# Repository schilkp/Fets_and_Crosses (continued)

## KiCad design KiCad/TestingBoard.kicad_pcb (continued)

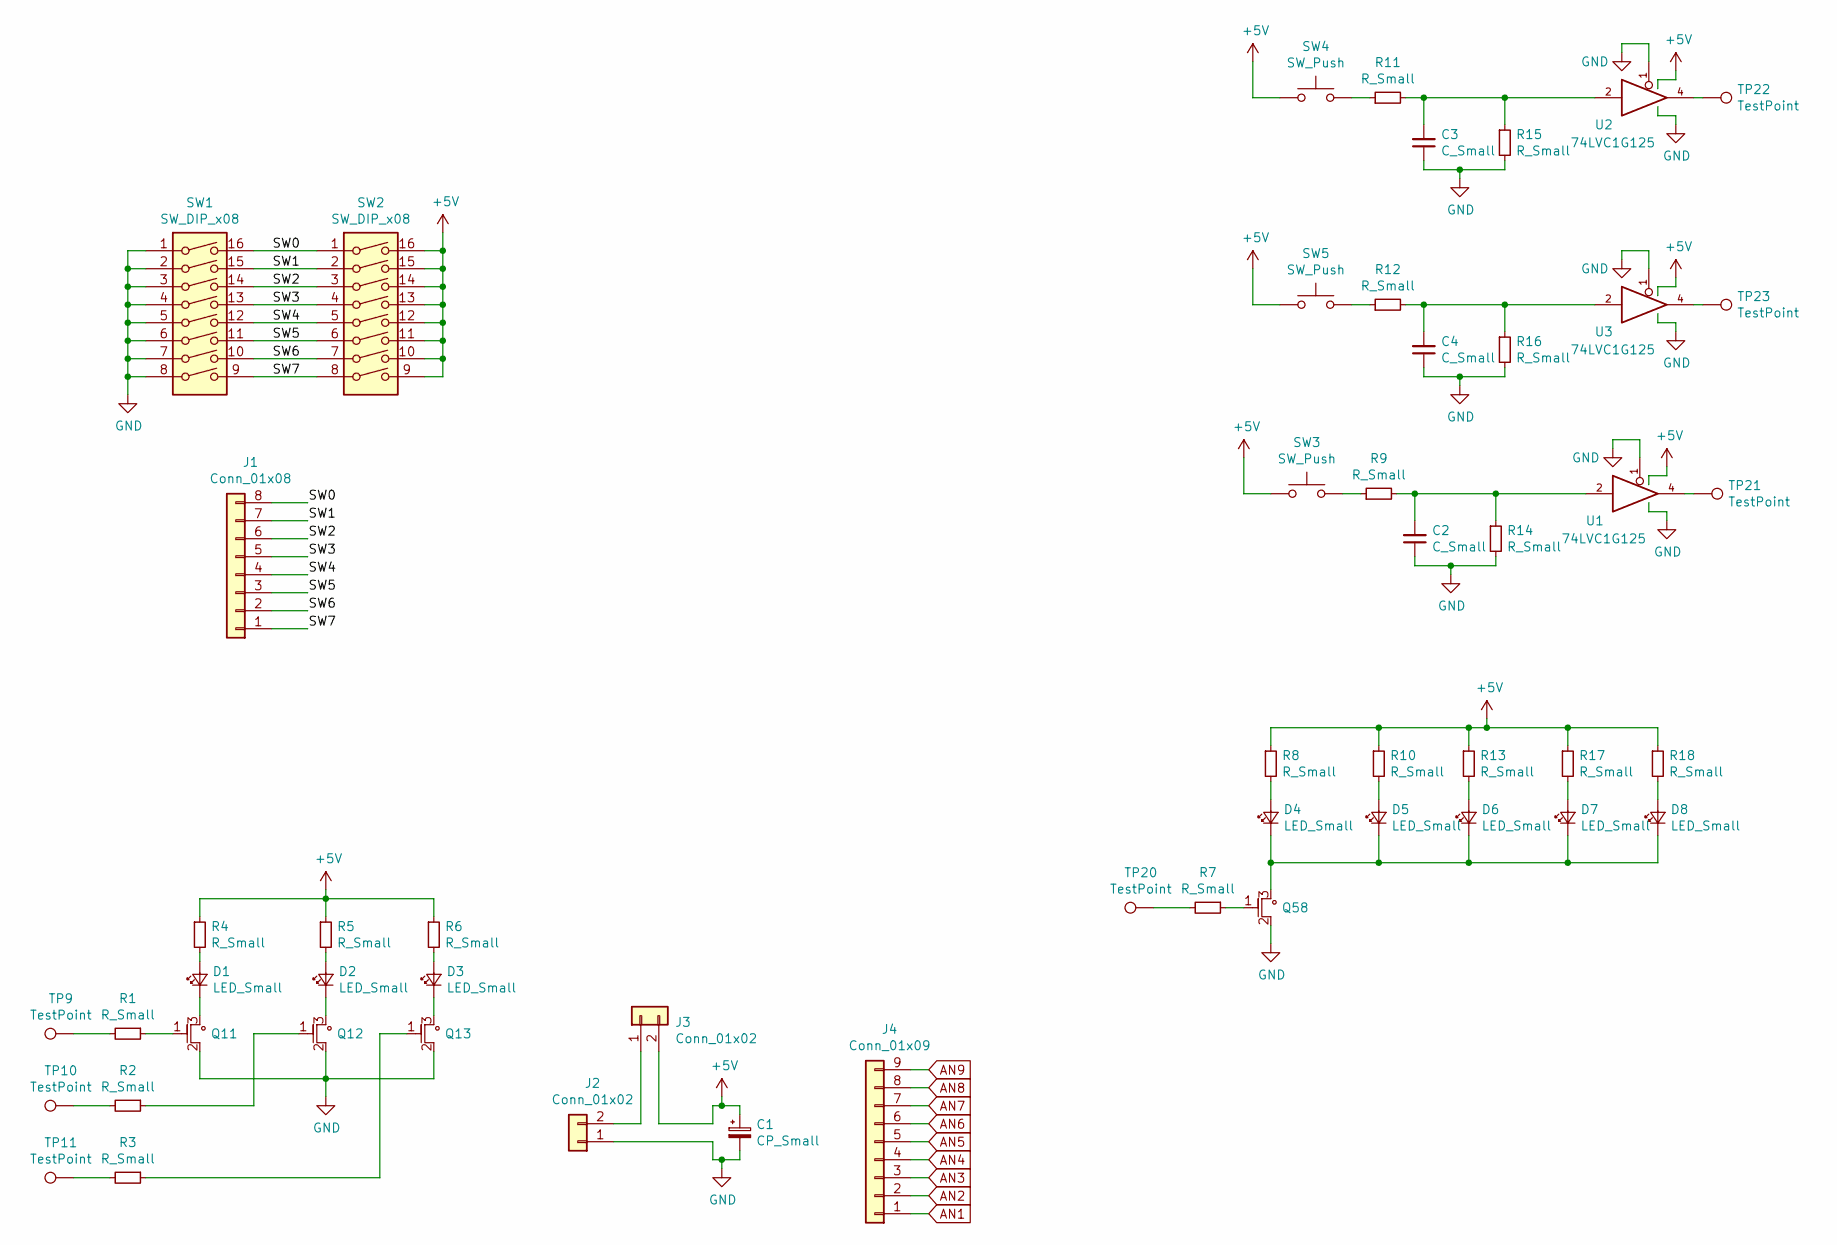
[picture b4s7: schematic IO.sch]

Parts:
C1: CP_Small; CP_Elec_8x6.5
C2, C3, C4: C_Small; C_0603_1608Metric
D1, D2, D3, D4, D5, D6, D7, D8: LED_Small; LED_0805_2012Metric
J1: Conn_01x08; PinHeader_1x08_P2.54mm_Vertical
J2, J3: Conn_01x02; PinHeader_1x02_P2.54mm_Vertical
J4: Conn_01x09; PinHeader_1x09_P2.54mm_Vertical
Q11, Q12, Q13, Q58: NM; SOT-23-N
R1, R2, R3, R4, R5, R6, R7, R8, R9, R10, R11, R12, R13, R14, R15, R16, R17, R18: R_Small; R_0603_1608Metric
SW1, SW2: SW_DIP_x08; DIP-16_W7.62mm
SW3, SW4, SW5: SW_Push; SW_PUSH_6mm
TP9, TP10, TP11, TP20, TP21, TP22, TP23: TestPoint; PinSocket_1x01_P2.54mm_Vertical
U1, U2, U3: 74LVC1G125; TSOP-5_1.65x3.05mm_P0.95mm

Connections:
+5V: C1.1, J3.2, R4.1, R5.1, R6.1, R8.1, R10.1, R13.1, R17.1, R18.1, SW2.9, SW2.10, SW2.11, SW2.12, SW2.13, SW2.14, SW2.15, SW2.16, SW3.1, SW4.1, SW5.1, U1.5 (VCC), U2.5 (VCC), U3.5 (VCC); also elsewhere on the board
/IO.sch/SW0: J1.8, SW1.16, SW2.1
/IO.sch/SW1: J1.7, SW1.15, SW2.2
/IO.sch/SW2: J1.6, SW1.14, SW2.3
/IO.sch/SW3: J1.5, SW1.13, SW2.4
/IO.sch/SW4: J1.4, SW1.12, SW2.5
/IO.sch/SW5: J1.3, SW1.11, SW2.6
/IO.sch/SW6: J1.2, SW1.10, SW2.7
/IO.sch/SW7: J1.1, SW1.9, SW2.8
AN1: J4.1; also elsewhere on the board
AN2: J4.2; also elsewhere on the board
AN3: J4.3; also elsewhere on the board
AN4: J4.4; also elsewhere on the board
AN5: J4.5; also elsewhere on the board
AN6: J4.6; also elsewhere on the board
AN7: J4.7; also elsewhere on the board
AN8: J4.8; also elsewhere on the board
AN9: J4.9; also elsewhere on the board
GND: C1.2, C2.1, C3.1, C4.1, J2.1, Q11.2, Q12.2, Q13.2, Q58.2, R14.2, R15.2, R16.2, SW1.1, SW1.2, SW1.3, SW1.4, SW1.5, SW1.6, SW1.7, SW1.8, U1.1, U1.3 (GND), U2.1, U2.3 (GND), U3.1, U3.3 (GND); also elsewhere on the board
unnamed: C2.2, R9.2, R14.1, U1.2
unnamed: C3.2, R11.2, R15.1, U2.2
unnamed: C4.2, R12.2, R16.1, U3.2
unnamed: D1.1 (K), Q11.3
unnamed: D1.2 (A), R4.2
unnamed: D2.1 (K), Q12.3
unnamed: D2.2 (A), R5.2
unnamed: D3.1 (K), Q13.3
unnamed: D3.2 (A), R6.2
unnamed: D4.1 (K), D5.1 (K), D6.1 (K), D7.1 (K), D8.1 (K), Q58.3
unnamed: D4.2 (A), R8.2
unnamed: D5.2 (A), R10.2
unnamed: D6.2 (A), R13.2
unnamed: D7.2 (A), R17.2
unnamed: D8.2 (A), R18.2
unnamed: J2.2, J3.1
unnamed: Q11.1, R1.1
unnamed: Q12.1, R2.1
unnamed: Q13.1, R3.1
unnamed: Q58.1, R7.1
unnamed: R1.2, TP9.1
unnamed: R2.2, TP10.1
unnamed: R3.2, TP11.1
unnamed: R7.2, TP20.1
unnamed: R9.1, SW3.2
unnamed: R11.1, SW4.2
unnamed: R12.1, SW5.2
unnamed: TP21.1, U1.4
unnamed: TP22.1, U2.4
unnamed: TP23.1, U3.4

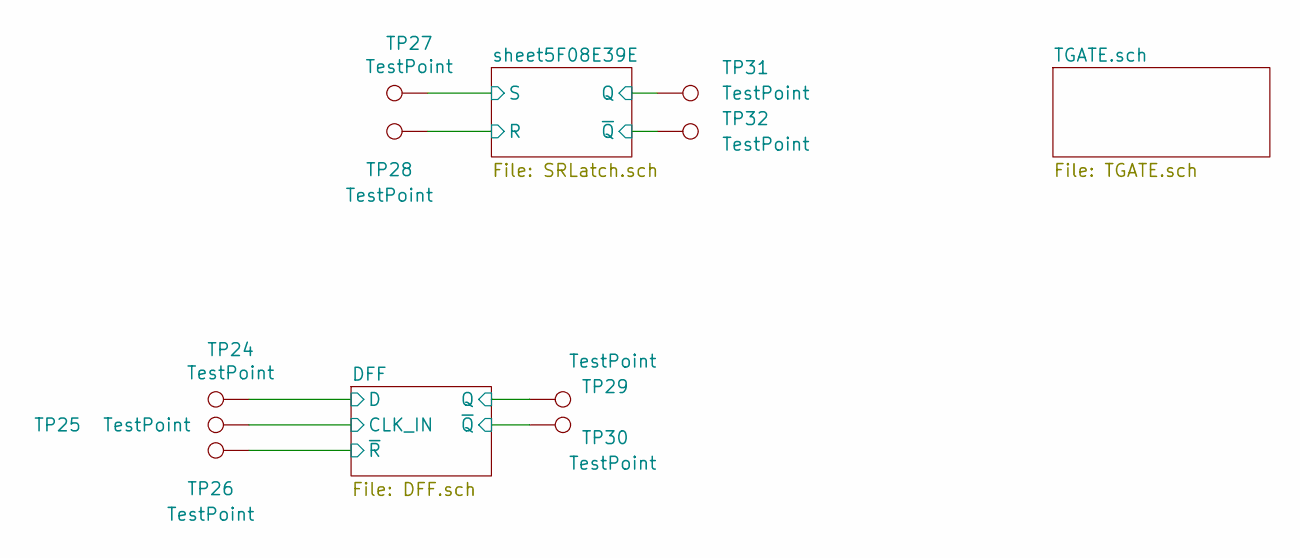
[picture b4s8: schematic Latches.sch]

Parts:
TP24, TP25, TP26, TP27, TP28, TP29, TP30, TP31, TP32: TestPoint; PinSocket_1x01_P2.54mm_Vertical

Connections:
/Sheet5F08E132/DFF/CLK_IN: TP25.1; also elsewhere on the board
/Sheet5F08E132/DFF/D: TP24.1; also elsewhere on the board
/Sheet5F08E132/DFF/Q: TP29.1; also elsewhere on the board
/Sheet5F08E132/DFF/~Q: TP30.1; also elsewhere on the board
/Sheet5F08E132/DFF/~R: TP26.1; also elsewhere on the board
/Sheet5F08E132/sheet5F08E39E/Q: TP31.1; also elsewhere on the board
/Sheet5F08E132/sheet5F08E39E/R: TP28.1; also elsewhere on the board
/Sheet5F08E132/sheet5F08E39E/S: TP27.1; also elsewhere on the board
/Sheet5F08E132/sheet5F08E39E/~Q: TP32.1; also elsewhere on the board

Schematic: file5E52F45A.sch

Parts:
Q97, Q99, Q100, Q101, Q102, Q103, Q104, Q105, Q106: PM; SOT-23-P
Q98, Q107, Q108, Q109, Q110, Q111, Q112, Q113, Q114: NM; SOT-23-N
R19, R20, R21, R22, R23, R24, R25, R26, R27, R28, R29, R30, R31, R32, R33, R34, R35, R36: R_Small; R_0603_1608Metric_NOLBL
TP38, TP39, TP40, TP41, TP42, TP43, TP44, TP45, TP46, TP47, TP48, TP49, TP50, TP51, TP52, TP53, TP54, TP55, TP56, TP57, TP58, TP59, TP60, TP61, TP62, TP63, TP64, TP65, TP66, TP67, TP68, TP69, TP70, TP71, TP72, TP73, TP74, TP75, TP76, TP77, TP78, TP79, TP80, TP81, TP82, TP83, TP84, TP85, TP86, TP87, TP88, TP89, TP90, TP91, TP92, TP93, TP94, TP95, TP96, TP97, TP98, TP99, TP100, TP101, TP102, TP103, TP104, TP105, TP106, TP107, TP108, TP109, TP110, TP111, TP112, TP113, TP114, TP115, TP116, TP117, TP118, TP119, TP120, TP121, TP122, TP123, TP124, TP125, TP126, TP127: TestPoint; TestPoint_Pad_1.5x1.5mm_NOLBL

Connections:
unnamed: Q97.1, TP38.1
unnamed: Q97.2, TP40.1
unnamed: Q97.3, TP39.1
unnamed: Q98.1, TP65.1
unnamed: Q98.2, TP69.1
unnamed: Q98.3, TP68.1
unnamed: Q99.1, TP41.1
unnamed: Q99.2, TP44.1
unnamed: Q99.3, TP43.1
unnamed: Q100.1, TP42.1
unnamed: Q100.2, TP46.1
unnamed: Q100.3, TP45.1
unnamed: Q101.1, TP47.1
unnamed: Q101.2, TP51.1
unnamed: Q101.3, TP50.1
unnamed: Q102.1, TP48.1
unnamed: Q102.2, TP53.1
unnamed: Q102.3, TP52.1
unnamed: Q103.1, TP49.1
unnamed: Q103.2, TP55.1
unnamed: Q103.3, TP54.1
unnamed: Q104.1, TP56.1
unnamed: Q104.2, TP60.1
unnamed: Q104.3, TP59.1
unnamed: Q105.1, TP57.1
unnamed: Q105.2, TP62.1
unnamed: Q105.3, TP61.1
unnamed: Q106.1, TP58.1
unnamed: Q106.2, TP64.1
unnamed: Q106.3, TP63.1
unnamed: Q107.1, TP66.1
unnamed: Q107.2, TP71.1
unnamed: Q107.3, TP70.1
unnamed: Q108.1, TP67.1
unnamed: Q108.2, TP73.1
unnamed: Q108.3, TP72.1
unnamed: Q109.1, TP74.1
unnamed: Q109.2, TP78.1
unnamed: Q109.3, TP77.1
unnamed: Q110.1, TP75.1
unnamed: Q110.2, TP80.1
unnamed: Q110.3, TP79.1
unnamed: Q111.1, TP76.1
unnamed: Q111.2, TP82.1
unnamed: Q111.3, TP81.1
unnamed: Q112.1, TP83.1
unnamed: Q112.2, TP87.1
unnamed: Q112.3, TP86.1
unnamed: Q113.1, TP84.1
unnamed: Q113.2, TP89.1
unnamed: Q113.3, TP88.1
unnamed: Q114.1, TP85.1
unnamed: Q114.2, TP91.1
unnamed: Q114.3, TP90.1
unnamed: R19.1, TP92.1
unnamed: R19.2, TP93.1
unnamed: R20.1, TP94.1
unnamed: R20.2, TP95.1
unnamed: R21.1, TP96.1
unnamed: R21.2, TP97.1
unnamed: R22.1, TP98.1
unnamed: R22.2, TP99.1
unnamed: R23.1, TP100.1
unnamed: R23.2, TP101.1
unnamed: R24.1, TP102.1
unnamed: R24.2, TP103.1
unnamed: R25.1, TP104.1
unnamed: R25.2, TP105.1
unnamed: R26.1, TP106.1
unnamed: R26.2, TP107.1
unnamed: R27.1, TP108.1
unnamed: R27.2, TP109.1
unnamed: R28.1, TP110.1
unnamed: R28.2, TP111.1
unnamed: R29.1, TP112.1
unnamed: R29.2, TP113.1
unnamed: R30.1, TP114.1
unnamed: R30.2, TP115.1
unnamed: R31.1, TP116.1
unnamed: R31.2, TP117.1
unnamed: R32.1, TP118.1
unnamed: R32.2, TP119.1
unnamed: R33.1, TP120.1
unnamed: R33.2, TP121.1
unnamed: R34.1, TP122.1
unnamed: R34.2, TP123.1
unnamed: R35.1, TP124.1
unnamed: R35.2, TP125.1
unnamed: R36.1, TP126.1
unnamed: R36.2, TP127.1

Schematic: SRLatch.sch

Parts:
Q59, Q60, Q65, Q66: NM; SOT-23-N
Q61, Q62, Q63, Q64: PM; SOT-23-P

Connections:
+5V: Q61.3, Q63.3; also elsewhere on the board
/Sheet5F08E132/sheet5F08E39E/Q: Q60.2, Q62.1, Q64.2, Q65.1, Q66.3; also elsewhere on the board
/Sheet5F08E132/sheet5F08E39E/R: Q59.1, Q61.1; also elsewhere on the board
/Sheet5F08E132/sheet5F08E39E/S: Q60.1, Q63.1; also elsewhere on the board
/Sheet5F08E132/sheet5F08E39E/~Q: Q59.2, Q62.2, Q64.1, Q65.3, Q66.1; also elsewhere on the board
GND: Q59.3, Q60.3, Q65.2, Q66.2; also elsewhere on the board
unnamed: Q61.2, Q62.3
unnamed: Q63.2, Q64.3

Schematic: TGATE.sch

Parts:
Q67, Q69, Q71: PM; SOT-23-P
Q68, Q70, Q72: NM; SOT-23-N
TP33, TP34, TP35, TP36, TP37: TestPoint; PinSocket_1x01_P2.54mm_Vertical

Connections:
+5V: Q67.3; also elsewhere on the board
GND: Q68.2; also elsewhere on the board
unnamed: Q67.1, Q68.1, Q70.1, Q72.1, TP33.1
unnamed: Q67.2, Q68.3, Q69.1, Q71.1
unnamed: Q69.2, Q70.3, TP34.1
unnamed: Q69.3, Q70.2, TP35.1
unnamed: Q71.2, Q72.2, TP36.1
unnamed: Q71.3, Q72.3, TP37.1

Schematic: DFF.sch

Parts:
Q73, Q76, Q77, Q80: PM; SOT-23-P
Q74, Q75, Q78, Q79: NM; SOT-23-N

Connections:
/Sheet5F08E132/DFF/CLK: Q73.1, Q75.1, Q78.1, Q80.1; also elsewhere on the board
/Sheet5F08E132/DFF/D: Q73.2, Q74.3; also elsewhere on the board
/Sheet5F08E132/DFF/NAND1/B: Q77.2, Q78.3; also elsewhere on the board
/Sheet5F08E132/DFF/NAND1/Y: Q75.2, Q76.3; also elsewhere on the board
/Sheet5F08E132/DFF/Sheet5F0BC752/IN: Q73.3, Q74.2, Q75.3, Q76.2; also elsewhere on the board
/Sheet5F08E132/DFF/sheet5F0D15F1/IN: Q77.3, Q78.2, Q79.3, Q80.2; also elsewhere on the board
/Sheet5F08E132/DFF/~CLK: Q74.1, Q76.1, Q77.1, Q79.1; also elsewhere on the board
/Sheet5F08E132/DFF/~Q: Q79.2, Q80.3; also elsewhere on the board

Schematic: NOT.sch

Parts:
Q81: PM; SOT-23-P
Q82: NM; SOT-23-N

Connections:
+5V: Q81.3; also elsewhere on the board
/Sheet5F08E132/DFF/NAND1/B: Q81.2, Q82.3; also elsewhere on the board
/Sheet5F08E132/DFF/Sheet5F0BC752/IN: Q81.1, Q82.1; also elsewhere on the board
GND: Q82.2; also elsewhere on the board

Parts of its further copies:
Q83, Q85, Q91: PM; SOT-23-P
Q84, Q86, Q92: NM; SOT-23-N

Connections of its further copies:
+5V: Q83.3, Q85.3, Q91.3; also elsewhere on the board
/Sheet5F08E132/DFF/CLK: Q85.2, Q86.3; also elsewhere on the board
/Sheet5F08E132/DFF/CLK_IN: Q83.1, Q84.1; also elsewhere on the board
/Sheet5F08E132/DFF/Q: Q91.2, Q92.3; also elsewhere on the board
/Sheet5F08E132/DFF/sheet5F0D15F1/IN: Q91.1, Q92.1; also elsewhere on the board
/Sheet5F08E132/DFF/~CLK: Q83.2, Q84.3, Q85.1, Q86.1; also elsewhere on the board
GND: Q84.2, Q86.2, Q92.2; also elsewhere on the board

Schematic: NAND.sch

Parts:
Q87, Q90: PM; SOT-23-P
Q88, Q89: NM; SOT-23-N

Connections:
+5V: Q87.3, Q90.3; also elsewhere on the board
/Sheet5F08E132/DFF/NAND1/B: Q88.1, Q90.1; also elsewhere on the board
/Sheet5F08E132/DFF/NAND1/Y: Q87.2, Q88.3, Q90.2; also elsewhere on the board
/Sheet5F08E132/DFF/~R: Q87.1, Q89.1; also elsewhere on the board
GND: Q89.2; also elsewhere on the board
unnamed: Q88.2, Q89.3

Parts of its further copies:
Q93, Q96: PM; SOT-23-P
Q94, Q95: NM; SOT-23-N

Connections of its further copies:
+5V: Q93.3, Q96.3; also elsewhere on the board
/Sheet5F08E132/DFF/Q: Q94.1, Q96.1; also elsewhere on the board
/Sheet5F08E132/DFF/~Q: Q93.2, Q94.3, Q96.2; also elsewhere on the board
/Sheet5F08E132/DFF/~R: Q93.1, Q95.1; also elsewhere on the board
GND: Q95.2; also elsewhere on the board
unnamed: Q94.2, Q95.3

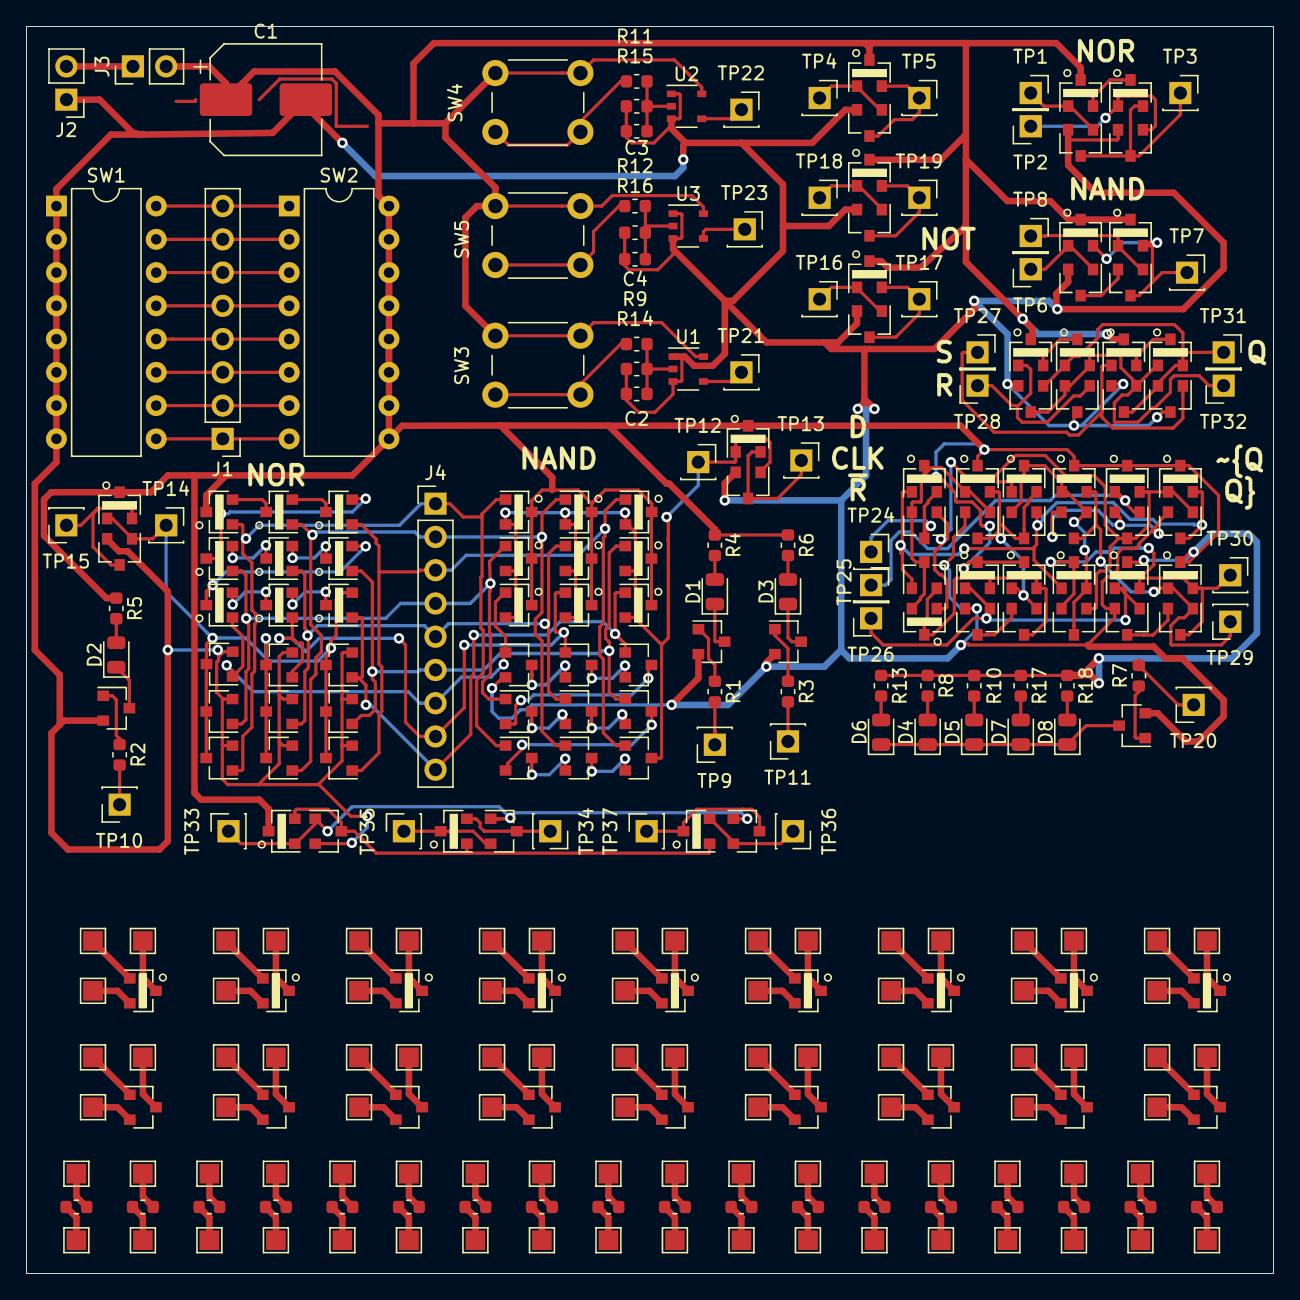
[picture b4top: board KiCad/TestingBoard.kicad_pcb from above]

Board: 2 copper layers, 95.2 x 95.2 mm, 301 parts (0 on the bottom side), 198 nets.

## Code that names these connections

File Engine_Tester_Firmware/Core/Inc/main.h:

/* USER CODE BEGIN Header */
/**
  ******************************************************************************
  * @file           : main.h
  * @brief          : Header for main.c file.
  *                   This file contains the common defines of the application.
  ******************************************************************************
  * @attention
  *
  * <h2><center>&copy; Copyright (c) 2021 STMicroelectronics.
  * All rights reserved.</center></h2>
  *
  * This software component is licensed by ST under BSD 3-Clause license,
  * the "License"; You may not use this file except in compliance with the
  * License. You may obtain a copy of the License at:
  *                        opensource.org/licenses/BSD-3-Clause
  *
  ******************************************************************************
  */
/* USER CODE END Header */

/* Define to prevent recursive inclusion -------------------------------------*/
#ifndef __MAIN_H
#define __MAIN_H

#ifdef __cplusplus
extern "C" {
#endif

/* Includes ------------------------------------------------------------------*/
#include "stm32f0xx_hal.h"

/* Private includes ----------------------------------------------------------*/
/* USER CODE BEGIN Includes */

/* USER CODE END Includes */

/* Exported types ------------------------------------------------------------*/
/* USER CODE BEGIN ET */

/* USER CODE END ET */

/* Exported constants --------------------------------------------------------*/
/* USER CODE BEGIN EC */
extern UART_HandleTypeDef huart1;
extern SPI_HandleTypeDef hspi1;
/* USER CODE END EC */

/* Exported macro ------------------------------------------------------------*/
/* USER CODE BEGIN EM */

/* USER CODE END EM */

/* Exported functions prototypes ---------------------------------------------*/
void Error_Handler(void);

/* USER CODE BEGIN EFP */

/* USER CODE END EFP */

/* Private defines -----------------------------------------------------------*/
#define LED1_Pin GPIO_PIN_0
#define LED1_GPIO_Port GPIOA
#define UART_TX_Pin GPIO_PIN_2
#define UART_TX_GPIO_Port GPIOA
#define UART_RX_Pin GPIO_PIN_3
#define UART_RX_GPIO_Port GPIOA
#define ENGINE_OUT_0_Pin GPIO_PIN_4
#define ENGINE_OUT_0_GPIO_Port GPIOA
#define ENGINE_OUT_1_Pin GPIO_PIN_5
#define ENGINE_OUT_1_GPIO_Port GPIOA
#define ENGINE_OUT_2_Pin GPIO_PIN_6
#define ENGINE_OUT_2_GPIO_Port GPIOA
#define ENGINE_OUT_3_Pin GPIO_PIN_7
#define ENGINE_OUT_3_GPIO_Port GPIOA
#define ENGINE_OUT_4_Pin GPIO_PIN_8
#define ENGINE_OUT_4_GPIO_Port GPIOA
#define ENGINE_OUT_5_Pin GPIO_PIN_9
#define ENGINE_OUT_5_GPIO_Port GPIOA
#define ENGINE_OUT_6_Pin GPIO_PIN_10
#define ENGINE_OUT_6_GPIO_Port GPIOA
#define ENGINE_OUT_7_Pin GPIO_PIN_11
#define ENGINE_OUT_7_GPIO_Port GPIOA
#define ENGINE_OUT_8_Pin GPIO_PIN_12
#define ENGINE_OUT_8_GPIO_Port GPIOA
#define OUT_CLK_Pin GPIO_PIN_3
#define OUT_CLK_GPIO_Port GPIOB
#define OUT_LATCH_Pin GPIO_PIN_4
#define OUT_LATCH_GPIO_Port GPIOB
#define OUT_DATA_Pin GPIO_PIN_5
#define OUT_DATA_GPIO_Port GPIOB
/* USER CODE BEGIN Private defines */

/* USER CODE END Private defines */

#ifdef __cplusplus
}
#endif

#endif /* __MAIN_H */

/************************ (C) COPYRIGHT STMicroelectronics *****END OF FILE****/

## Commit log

2020-02-13 Added Matlab code for generating aiROM content
2020-02-13 Added Logisim Simulation
2020-02-14 Adding TestingBoard
    Prototype board to test subsections of the prototype.
2020-02-14 Updated gitignore for Matlab's .asv autosave files
2020-02-14 Change AI ROM Output Encoding
    Change AI ROM Output Encoding
    Old Encoding Scheme enumerated the 9 possible Tic Tac Toe moves as binary numbers
    0 - 8, occupying the lower 4 bits of the 8 bit ROM.
    This however required some decode circuitry.
    The New encoding scheme maps each bit of the 8 bit ROM output to the first 8 slots of the Tic Tac Toe Board, and the 9th remaining slot to 0 (no bits active).
    This greatly reduces the number of gates and transistors needed to a single 9-input NOR gate to detect the 9th board slot.
2020-02-18 First README.md draft
2020-02-19 Created StateMachine_Encoding.md
    Includes all implementation details of new optimized Statemachine:
    - State Transition Diagram
    - States & State Encoding
    - Inputs & Input Encoding
    - Outputs & Output Decoding
    - State Transition Diagram
2020-02-19 Implemented new optimized StateMachine in Logisim
2020-02-20 Updated ROM_StateMachine for new StateMachien Architecture
2020-02-20 Added LICENSE
2020-02-20 Changed StateTransition from ROM to Logic
2020-02-20 Fixed bug in "MoveOK" logic that let P1 play an empty opening move
2020-02-20 Fixed Bug in Memory Gen: sometimes CPU played illegal/bad moves
2020-02-20 Optimized Move-OK Circuitry to use approx 32 fewer Qs
2020-02-20 Optimized Win-Detect to use approx 36 fewer Qs
2020-02-20 Optimized Draw-Detect to use approx 20 fewer Qs
2020-02-20 Removed Move-Select Mem. Save 200+ Qs!
2020-02-23 Optimized P2-Select, saves approx 38 Qs
2020-02-26 Slightly rearranged gates to group related logic
2020-02-26 TestingBoard_v0.1 Commit
    Schematic first draft
    Sync
2020-02-28 Added Matlab script to generate binary files
2020-03-01 Updated MemoryGen code & Simulation to reflect actual memory size
2020-03-01 Added small notes on how to start/operate simulation
2020-03-01 Fixed bug in MemoryGen code that populated unused half of memory
2020-03-05 Added Logic to dis-allow move if more than one field select
2020-03-19 Slight README Updates
2020-05-29 Optimized Move Selected OK
2020-07-01 New Statemachine/clocking working
2020-07-01 Cleanup
2020-07-01 First Draft
2020-07-01 Setup KiCad Project
2020-07-01 Reworked everything to use Buses
2020-07-05 Schematic Done, Footprints assigned, ERC OK.
2020-07-05 Schematic fixes.
2020-07-05 PCB v0.0 done, production files generated.
2020-07-05 Removed old encoding documentation.
2020-08-25 Readme Spelling
2020-08-27 Changed Player Mem Does not use MUX and has fewer Qs
2020-08-27 Placed MUXes
2020-08-27 First Draft Schematic Updates
2020-08-27 Layout: Spacing done, 1 BoardCell ready
2020-08-27 First Layout draft done.
2020-08-28 Overlap check done.
2020-08-28 Generated Production Files (v0.1)
2020-08-28 Added changelog
2020-09-15 Fixed 'DRAW' Led in simulation.
2020-09-15 Updated Schematic
    - Fixed Mem cell
    - Fixed Draw LED to not light if last move wins game
    - Changed capacitor
2020-09-16 Updated PCB Layout
2020-09-16 Generated Production Files
2020-09-16 Updated changelog v0.2
2020-10-31 Ignore HTML in language stats
2020-10-31 Readme Update
2020-11-01 Ignore HTMLs for lanugage stats, really now.
2021-02-06 Implemented previous computer/testbench in python
2021-02-06 Slight refactor
2021-02-07 Implemented reference min/max engine
2021-02-07 Refactor
2021-02-08 Added engine_improved
2021-02-09 ROM Generation Script
2021-02-23 TicTacToe Engine working in simulation
2021-02-23 Added switch between engine/ROM
2021-03-06 PCB v1.0 layout mostly done.
2021-03-06 vim files
2021-03-06 Fixed Win-LEDs swapped.
2021-03-06 First Engine Draft
2021-03-09 Finished layout draft of main PCB
    ERC is good, still need to check for via in pad (and silkscreen)
2021-03-09 Small fixes
2021-03-31 Engine ready for validation+layout
2021-03-31 Changed to female connectors
    Layout finished, still need to do via-in-pad/silk checks
2021-03-31 Small engine fix
2021-04-04 Engine Fixes
2021-04-04 Ready for Engine Layout
2021-04-04 Engine: pre Not-replication
2021-04-04 Engine: Not Replicated
2021-04-04 Engine: Pre 4in Nor replicate
2021-04-04 Engine: Post 4in nor replication
2021-04-04 Engine: Pre 2in NOR replication
2021-04-04 Engine: Post 2in NOR replication
2021-04-04 Engine: Pre 2in OR replication
2021-04-04 Engine: Post 2in OR replication
2021-04-04 Engine: Pre 3-in Cell replication
2021-04-04 Engine: Post 3-in cell replication
2021-04-04 Engine: Pre 2in Cell replication
2021-04-04 Engine: Post 2in Cell replication
2021-04-04 Engine: Pre 1in Cell replication
2021-05-09 Automatic Python formatting+hooks
2021-05-09 Engine: Post 1in Cell replication
2021-05-23 Removed MATLAB scripts, we are all python now
2021-05-23 Engine layout.
2021-05-23 Generated main pcb v1.0 produciton files.
2021-05-23 Documentation work
2021-05-23 Generated engine pcb production files.
2021-05-23 Renamed to ECAD folder.
2021-05-23 Engine test layout + production files v1.0
2021-05-23 File Name error
2021-05-31 Added PCB dimensions in KiCad
2021-06-01 Most of python work for hardware_bridge done.
2021-06-01 Pulled in psPROG as base for tester firmware
2021-06-10 First working hardware bridge draft
2021-06-11 Improved/Fixed testing
2021-06-12 Further improved hardware bridge test
2021-06-12 Changelog update
2021-06-20 hardware_bridge debug output
2021-09-05 Fixed off-by-one error in serial port selection
2021-09-14 Small tooling change
    Using setup.cfg to mark python/project root. That is much more standard
    than .coc_root
2021-09-14 Small cleanup
2021-09-20 Small README update + spellfix
2021-09-20 Added Picture
2022-02-06 POR, Tooling Holes
2022-02-06 Seperated Red/Green LEDs
2022-02-06 Engine: Added Tooling Holes, LCSC Part numbers
2022-02-06 Added Most LCSC Part Numbers
2022-02-07 Generated Engine v1.1 Production Files
2022-02-07 Specified LED Resisitors
2022-02-07 Generated v1.1 Production Files
2022-02-07 Fixedup version numbers
2022-02-07 Renamed files, added CSVs
